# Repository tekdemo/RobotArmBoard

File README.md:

# Robot Arm Control Board

Teensy based control board designed for adding closed loop control to OWI-535 Robotic Arm Edge kit. 

## Setup

### Power
Using the 6 D cell battery output is suggested. See assembly notes for more details.

The Teensy is not powered by the batteries, and must be provided USB power for the robot to operate. 

### Motors

Each motor is driven by a pair of signal pins signals from the Teensy. Setting one `HIGH` and the other `LOW` will result in moving the motor, and thus each joint. 

- Pins `10` and `9` control `M1`, opening and closing the claw.
- Pins `6` and `5` control `M2`, the "wrist" joint
- Pins `4` and `3` control `M3`, the "elbow" joint. 
- Pins `20` and `21` control `M4`, the "shoulder" joint. 
- Pins `22` and `23` control `M5`, which rotates the arm 
- Pin `13` controls the light on the claw end. This is the same as the Teensy's built in LED.

### Analog Feedback

For closed loop feedback, the following pins are available:
- Pin `A1` corresponds to `M1`'s potentiometer. 
- Pin `A2` corresponds to `M2`'s potentiometer. 
- Pin `A3` corresponds to `M3`'s potentiometer. 
- Pin `A4` corresponds to `M4`'s potentiometer. 
- Pin `A5` corresponds to `M5`'s potentiometer. 

Note, each potentiometer "tuning" will be somewhat different, and require some setup for each robot and each joint. 

### Controller Input
The controller uses the same analog pins as the Analog feedback. As a result, it's not simple to use the controller for input when the analog feedback is plugged in. However, doing so will not harm the electronics. 

- Pin `A1` corresponds to `M1`'s joystick. 
- Pin `A2` corresponds to `M2`'s joystick. 
- Pin `A3` corresponds to `M3`'s joystick. 
- Pin `A4` corresponds to `M4`'s joystick. 
- Pin `A5` corresponds to `M5`'s joystick. 
- Pin `A0` corresponds to the Light slider. 

Due to the joystick construction the joystick will only generate a few values. When read using `AnalogRead`, you will get roughly `512` when the joystick is idle, and around `1023` or `0` when the joystick is pressed. 

The LED switch is wired up to it's own unique input, and can be used alongside a closed loop input without issue. The `LED` switch will be around `512` when off, and `1023` when on.

## Assembly

### Power Input

### Motors

### Controller Input Section

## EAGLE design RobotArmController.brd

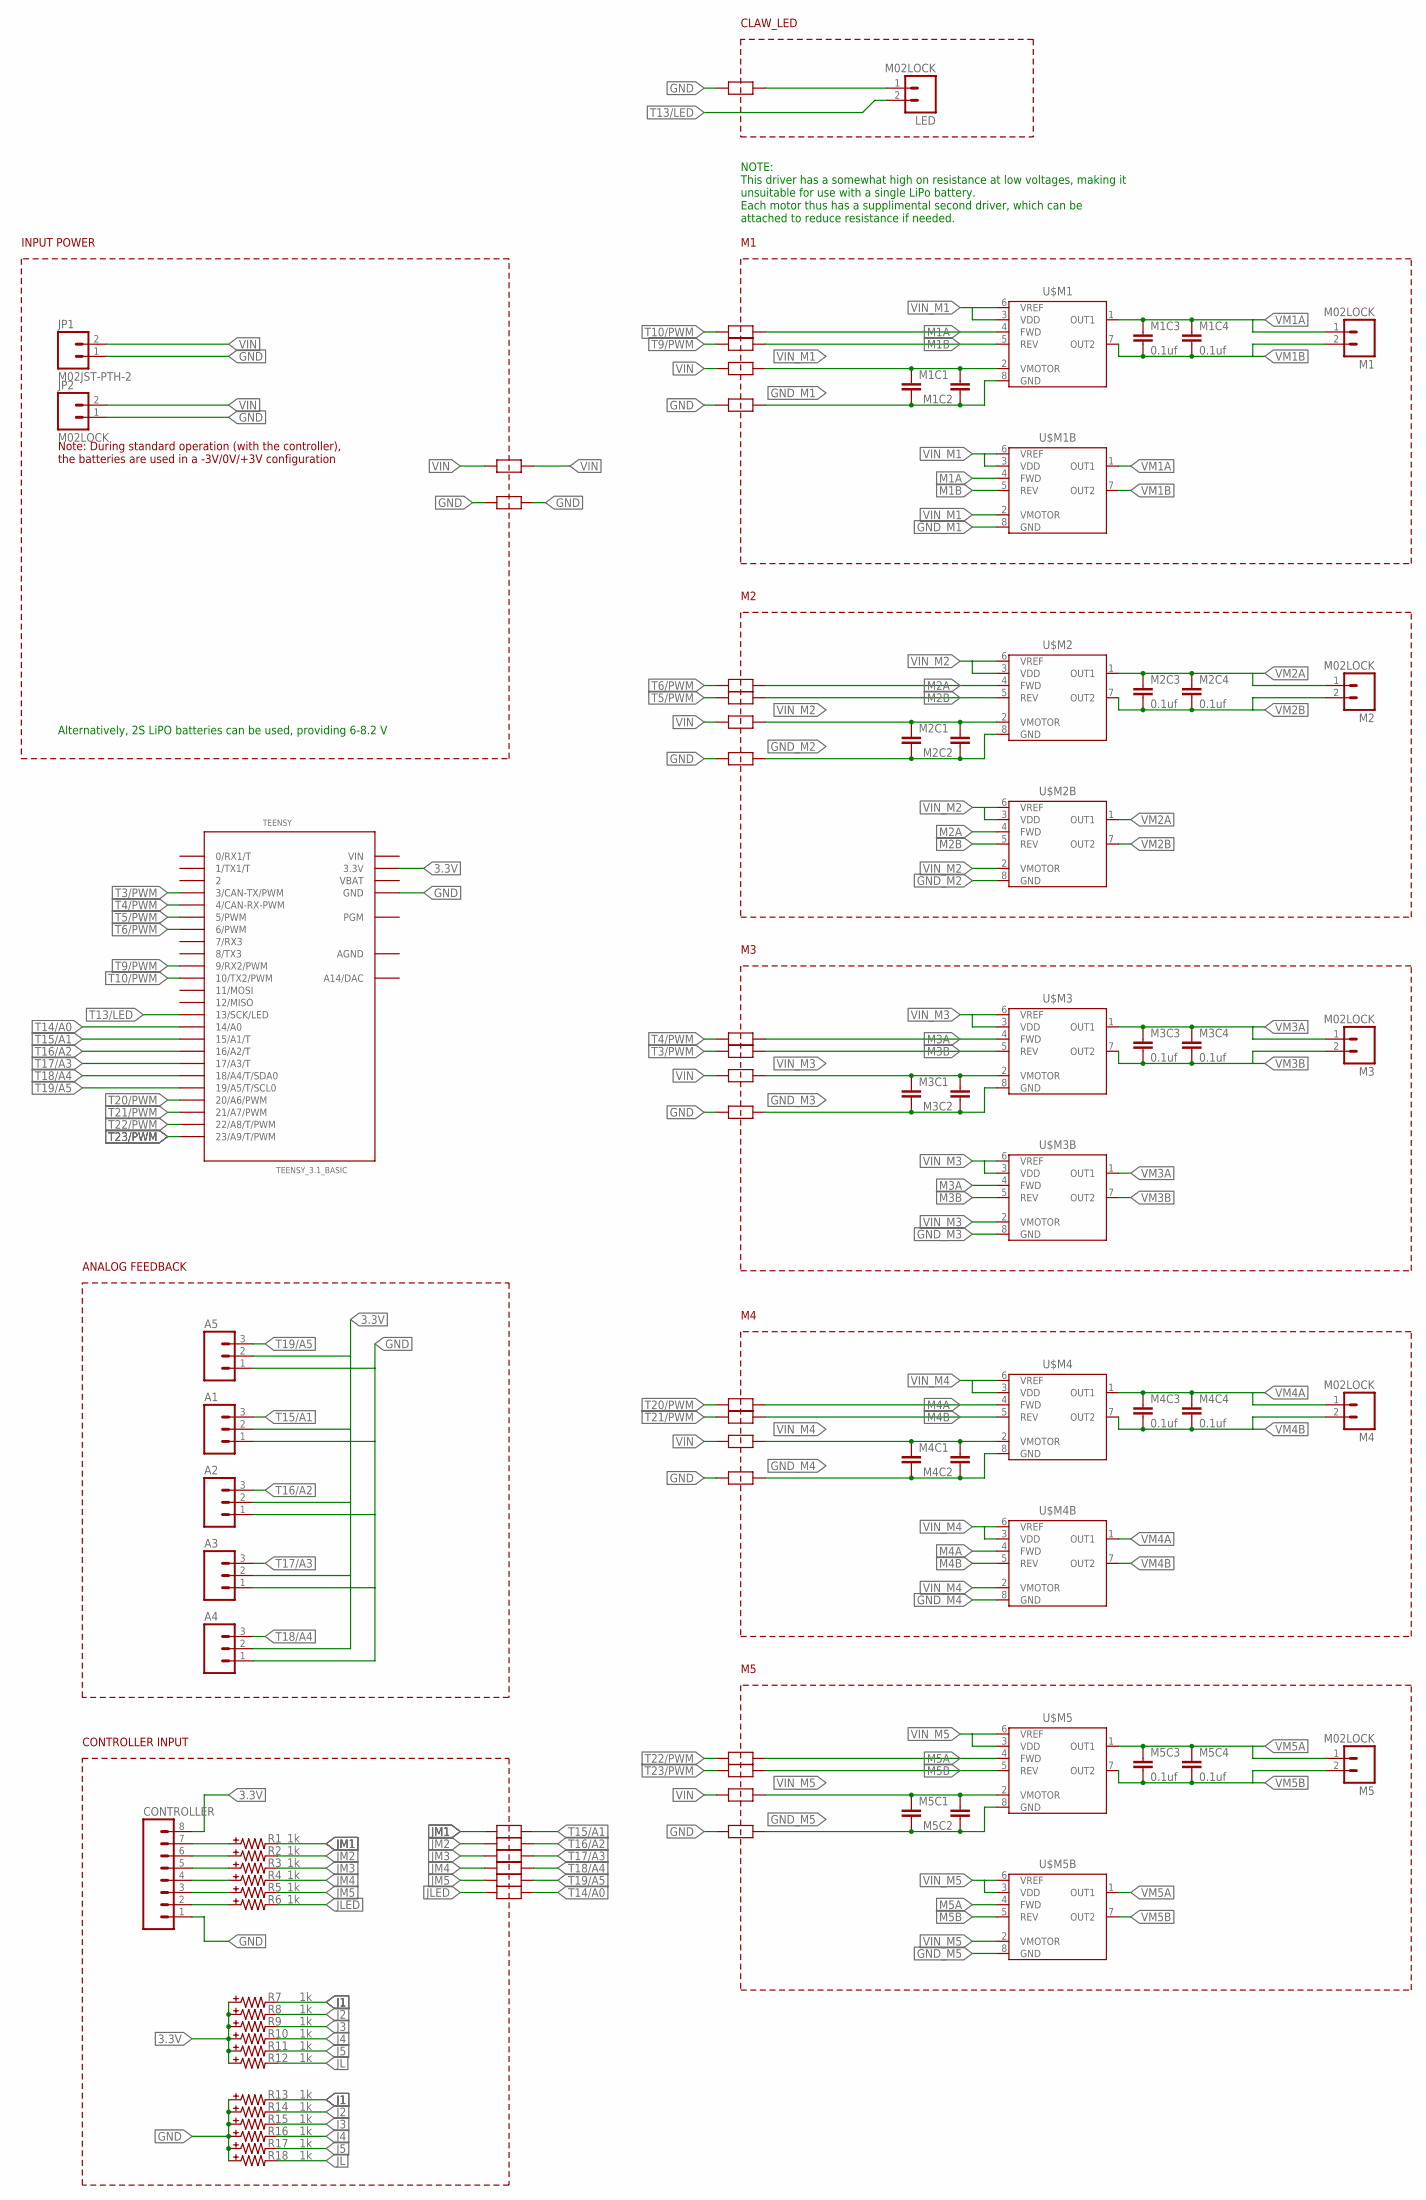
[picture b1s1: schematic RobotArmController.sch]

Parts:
A1, A2, A3, A4, A5: M03LOCK; 1X03_LOCK
CONTROLLER: M08LOCK; 1X08_LOCK
JP1: M02JST-PTH-2; JST-2-PTH
JP2: M02LOCK; 1X02_LOCK
LED: M02LOCK; 1X02_LOCK
M1, M2, M3, M4, M5: M02LOCK; 1X02_LOCK
M1C1, M2C1, M3C1, M4C1, M5C1: CAP1210; 1210
M1C2, M2C2, M3C2, M4C2, M5C2: CAPUNIVERSAL; 0402-0603-0805-UNIVERSAL
M1C3, M1C4, M2C3, M2C4, M3C3, M3C4, M4C3, M4C4, M5C3, M5C4: 0.1uf; 0402-0603-0805-UNIVERSAL
R1, R2, R3, R4, R5, R6, R7, R8, R9, R10, R11, R12, R13, R14, R15, R16, R17, R18: 1k; 0402-0603-0805-UNIVERSAL
TEENSY: TEENSY_3.1_BASIC
U$1, U$2, U$3, U$4, U$5, U$6, U$7, U$8, U$9, U$10, U$11, U$12, U$13, U$14, U$15, U$16, U$17, U$18, U$19, U$20, U$21, U$22, U$23, U$24, U$25, U$26, U$27, U$28, U$29: NET-JUNCTION-2
U$M1, U$M1B, U$M2, U$M2B, U$M3, U$M3B, U$M4, U$M4B, U$M5, U$M5B: ZXBM5210; SO08

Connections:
3.3V: A1.2, A2.2, A3.2, A4.2, A5.2, CONTROLLER.8, R7.+ (1), R8.+ (1), R9.+ (1), R10.+ (1), R11.+ (1), R12.+ (1), TEENSY.3.3V, TEENSY.3.3V1 (3.3V)
AGND: TEENSY.AGND
GND: A1.1, A2.1, A3.1, A4.1, A5.1, CONTROLLER.1, JP1.1, JP2.1, LED.1, R13.+ (1), R14.+ (1), R15.+ (1), R16.+ (1), R17.+ (1), R18.+ (1), TEENSY.GND, TEENSY.GND1 (GND), U$2.P$1, U$5.P$1, U$7.P$1, U$9.P$1, U$11.P$1, U$13.P$1, U$13.P$2, U$24.P$1, U$24.P$2
GND_M1: M1C1.2, M1C2.- (1), U$2.P$2, U$M1.8 (GND), U$M1B.8 (GND)
GND_M2: M2C1.2, M2C2.- (1), U$5.P$2, U$M2.8 (GND), U$M2B.8 (GND)
GND_M3: M3C1.2, M3C2.- (1), U$7.P$2, U$M3.8 (GND), U$M3B.8 (GND)
GND_M4: M4C1.2, M4C2.- (1), U$9.P$2, U$M4.8 (GND), U$M4B.8 (GND)
GND_M5: M5C1.2, M5C2.- (1), U$11.P$2, U$M5.8 (GND), U$M5B.8 (GND)
J1: CONTROLLER.7, R1.+ (1), R7.- (2), R13.- (2)
J2: CONTROLLER.6, R2.+ (1), R8.- (2), R14.- (2)
J3: CONTROLLER.5, R3.+ (1), R9.- (2), R15.- (2)
J4: CONTROLLER.4, R4.+ (1), R10.- (2), R16.- (2)
J5: CONTROLLER.3, R5.+ (1), R11.- (2), R17.- (2)
JL: CONTROLLER.2, R6.+ (1), R12.- (2), R18.- (2)
JLED: R6.- (2), U$29.P$1
JM1: R1.- (2), U$12.P$1
JM2: R2.- (2), U$25.P$1
JM3: R3.- (2), U$26.P$1
JM4: R4.- (2), U$27.P$1
JM5: R5.- (2), U$28.P$1
M1A: U$14.P$2, U$M1.4 (FWD), U$M1B.4 (FWD)
M1B: U$15.P$2, U$M1.5 (REV), U$M1B.5 (REV)
M2A: U$16.P$2, U$M2.4 (FWD), U$M2B.4 (FWD)
M2B: U$17.P$2, U$M2.5 (REV), U$M2B.5 (REV)
M3A: U$18.P$2, U$M3.4 (FWD), U$M3B.4 (FWD)
M3B: U$19.P$2, U$M3.5 (REV), U$M3B.5 (REV)
M4A: U$20.P$2, U$M4.4 (FWD), U$M4B.4 (FWD)
M4B: U$21.P$2, U$M4.5 (REV), U$M4B.5 (REV)
M5A: U$22.P$2, U$M5.4 (FWD), U$M5B.4 (FWD)
M5B: U$23.P$2, U$M5.5 (REV), U$M5B.5 (REV)
T3/PWM: TEENSY.3 (3/CAN-TX/PWM), U$19.P$1
T4/PWM: TEENSY.4 (4/CAN-RX-PWM), U$18.P$1
T5/PWM: TEENSY.5 (5/PWM), U$17.P$1
T6/PWM: TEENSY.6 (6/PWM), U$16.P$1
T9/PWM: TEENSY.9 (9/RX2/PWM), U$15.P$1
T10/PWM: TEENSY.10 (10/TX2/PWM), U$14.P$1
T13/LED: LED.2, TEENSY.13 (13/SCK/LED)
T14/A0: TEENSY.14/A0, U$29.P$2
T15/A1: A1.3, TEENSY.15/A1 (15/A1/T), U$12.P$2
T16/A2: A2.3, TEENSY.16/A2 (16/A2/T), U$25.P$2
T17/A3: A3.3, TEENSY.17/A3 (17/A3/T), U$26.P$2
T18/A4: A4.3, TEENSY.18/A4 (18/A4/T/SDA0), U$27.P$2
T19/A5: A5.3, TEENSY.19/A5 (19/A5/T/SCL0), U$28.P$2
T20/PWM: TEENSY.20/A6 (20/A6/PWM), U$20.P$1
T21/PWM: TEENSY.21/A7 (21/A7/PWM), U$21.P$1
T22/PWM: TEENSY.22/A8 (22/A8/T/PWM), U$22.P$1
T23/PWM: TEENSY.23/A9 (23/A9/T/PWM), U$23.P$1
VBAT: TEENSY.VBAT
VIN: JP1.2, JP2.2, TEENSY.VIN, U$1.P$1, U$3.P$1, U$4.P$1, U$4.P$2, U$6.P$1, U$8.P$1, U$10.P$1
VIN_M1: M1C1.1, M1C2.+ (2), U$1.P$2, U$M1.2 (VMOTOR), U$M1.3 (VDD), U$M1.6 (VREF), U$M1B.2 (VMOTOR), U$M1B.3 (VDD), U$M1B.6 (VREF)
VIN_M2: M2C1.1, M2C2.+ (2), U$3.P$2, U$M2.2 (VMOTOR), U$M2.3 (VDD), U$M2.6 (VREF), U$M2B.2 (VMOTOR), U$M2B.3 (VDD), U$M2B.6 (VREF)
VIN_M3: M3C1.1, M3C2.+ (2), U$6.P$2, U$M3.2 (VMOTOR), U$M3.3 (VDD), U$M3.6 (VREF), U$M3B.2 (VMOTOR), U$M3B.3 (VDD), U$M3B.6 (VREF)
VIN_M4: M4C1.1, M4C2.+ (2), U$8.P$2, U$M4.2 (VMOTOR), U$M4.3 (VDD), U$M4.6 (VREF), U$M4B.2 (VMOTOR), U$M4B.3 (VDD), U$M4B.6 (VREF)
VIN_M5: M5C1.1, M5C2.+ (2), U$10.P$2, U$M5.2 (VMOTOR), U$M5.3 (VDD), U$M5.6 (VREF), U$M5B.2 (VMOTOR), U$M5B.3 (VDD), U$M5B.6 (VREF)
VM1A: M1.1, M1C3.- (1), M1C4.- (1), U$M1.1 (OUT1), U$M1B.1 (OUT1)
VM1B: M1.2, M1C3.+ (2), M1C4.+ (2), U$M1.7 (OUT2), U$M1B.7 (OUT2)
VM2A: M2.1, M2C3.- (1), M2C4.- (1), U$M2.1 (OUT1), U$M2B.1 (OUT1)
VM2B: M2.2, M2C3.+ (2), M2C4.+ (2), U$M2.7 (OUT2), U$M2B.7 (OUT2)
VM3A: M3.1, M3C3.- (1), M3C4.- (1), U$M3.1 (OUT1), U$M3B.1 (OUT1)
VM3B: M3.2, M3C3.+ (2), M3C4.+ (2), U$M3.7 (OUT2), U$M3B.7 (OUT2)
VM4A: M4.1, M4C3.- (1), M4C4.- (1), U$M4.1 (OUT1), U$M4B.1 (OUT1)
VM4B: M4.2, M4C3.+ (2), M4C4.+ (2), U$M4.7 (OUT2), U$M4B.7 (OUT2)
VM5A: M5.1, M5C3.- (1), M5C4.- (1), U$M5.1 (OUT1), U$M5B.1 (OUT1)
VM5B: M5.2, M5C3.+ (2), M5C4.+ (2), U$M5.7 (OUT2), U$M5B.7 (OUT2)

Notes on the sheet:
INPUT POWER
Note: During standard operation (with the controller), the batteries are used in a -3V/0V/+3V configuration
Alternatively, 2S LiPO batteries can be used, providing 6-8.2 V
NOTE: This driver has a somewhat high on resistance at low voltages, making it unsuitable for use with a single LiPo battery. Each motor thus has a supplimental second driver, which can be attached to reduce resistance if needed.
CLAW_LED
ANALOG FEEDBACK
CONTROLLER INPUT

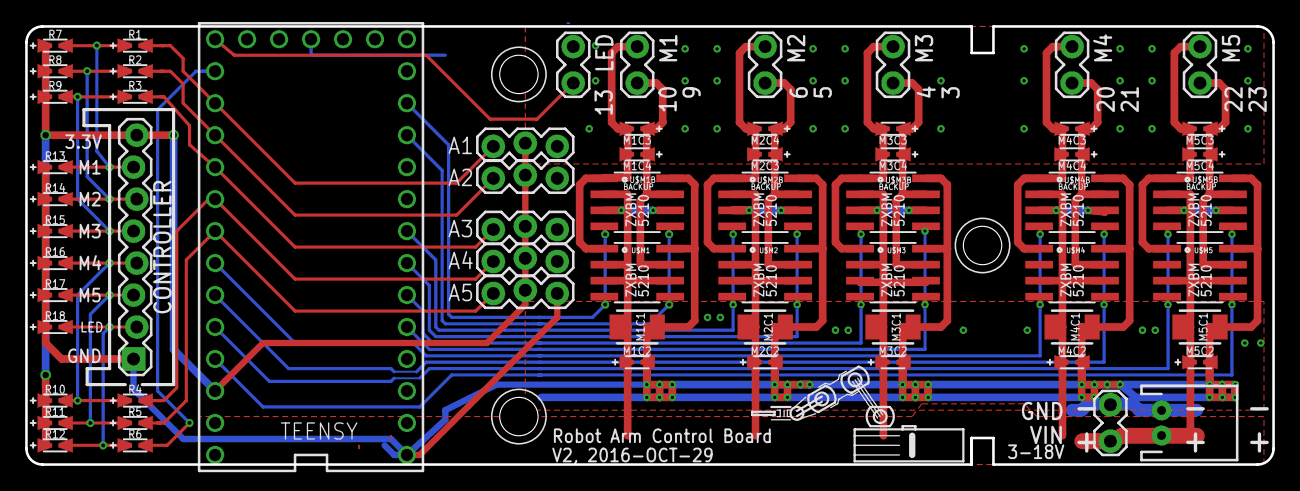
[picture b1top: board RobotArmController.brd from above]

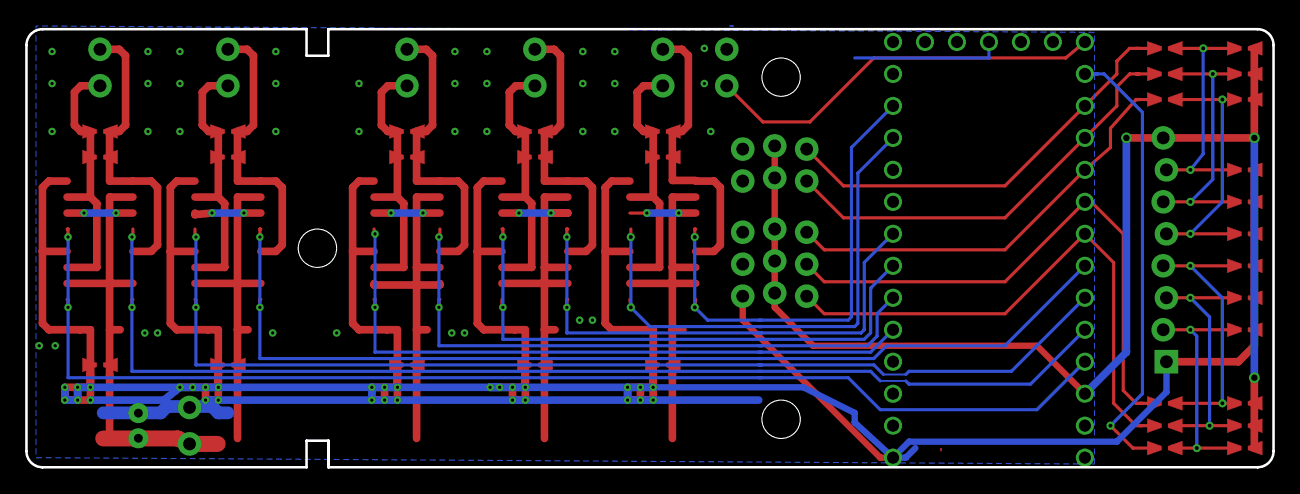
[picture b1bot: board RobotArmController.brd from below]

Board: 2 copper layers, 99.1 x 34.8 mm, 92 parts (12 on the bottom side), 62 nets.

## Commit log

2016-10-24 Draw schematic
2016-10-24 Route motor drivers
2016-10-24 Route + Define mechanical
2016-10-24 Wire to teensy
2016-10-24 Adjust for silkscreen and labels
2016-10-29 Correct mounting slot errors
2016-10-29 Remove LED resistor (not used)
2016-10-29 Add OWI power connector, update gnd plane, silk
2016-10-31 Add controller input
2016-10-31 Basic docs

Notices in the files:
parts and their libraries:
SparkFun-Connectors: Licensing: Creative Commons ShareAlike 4.0 International - https://creativecommons.org/licenses/by-sa/4.0
